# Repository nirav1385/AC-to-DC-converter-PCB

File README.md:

# ⚡ 12V AC to DC Converter — Full Bridge Rectifier PCB

A compact, through-hole **12V AC to DC converter** PCB designed in **KiCad 10.0**. This project converts 12V AC input into smooth DC output using a full-bridge rectifier with filtering, and includes a power indicator LED.

## 📸 Project Photos

### Schematic Diagram

### PCB Layout

### 3D View of PCB

---

## 📋 Table of Contents

- [Project Photos](#-project-photos)
- [Features](#-features)
- [Circuit Description](#-circuit-description)
- [Schematic Overview](#-schematic-overview)
- [Bill of Materials (BOM)](#-bill-of-materials-bom)
- [PCB Details](#-pcb-details)
- [How It Works](#-how-it-works)
- [Getting Started](#-getting-started)
- [Manufacturing](#-manufacturing)
- [Safety Warning](#%EF%B8%8F-safety-warning)
- [License](#-license)

---

## ✨ Features

- 🔌 **Full-bridge rectifier** using 4x 1N4007 diodes for efficient AC to DC conversion
- 🔋 **1000µF electrolytic capacitor** for smooth, ripple-free DC output
- 💡 **LED power indicator** with current-limiting resistor — know at a glance when the circuit is ON
- 🔩 **Screw terminal connectors** for easy and secure wire connections (both AC input & DC output)
- 📐 **Compact through-hole (THT) design** — easy to solder by hand, beginner-friendly
- 📦 **Gerber files included** — ready for PCB fabrication
- 🛠️ **Designed in KiCad 10.0** — fully open-source EDA tool

---

## 🔍 Circuit Description

This is a classic **unregulated AC to DC power supply** circuit. It takes a 12V AC input (typically from a step-down transformer) and converts it to approximately **~15-17V DC** (peak voltage minus diode drops) using a full-bridge rectifier.

---

## 📐 Schematic Overview

The circuit consists of the following stages:

### 1. AC Input Stage
- **J1** — Screw Terminal (2-pin) for 12V AC input from a transformer

### 2. Full-Bridge Rectifier
- **D1, D2, D3, D4** — 1N4007 (1000V, 1A) rectifier diodes arranged in a bridge configuration
- Converts both halves of the AC waveform into pulsating DC

### 3. Filtering Stage
- **C1** — 1000µF electrolytic capacitor
- Smooths the pulsating DC into a nearly constant DC voltage
- Reduces output ripple significantly

### 4. Bleeder/Discharge Resistor
- **R1** — 10kΩ resistor connected across the output
- Safely discharges the capacitor when the circuit is turned off
- Provides a minimum load for stability

### 5. Power Indicator
- **R2** — 2.2kΩ current-limiting resistor
- **D5** — LED (5mm, through-hole)
- Indicates that DC power is present at the output

### 6. DC Output Stage
- **J2** — Screw Terminal (2-pin) for DC output (+VE and -VE)

---

## 📦 Bill of Materials (BOM)

| Ref | Component | Value | Package/Footprint | Qty | Description |
|-----|-----------|-------|--------------------|-----|-------------|
| D1, D2, D3, D4 | 1N4007 | - | DO-41 (THT) | 4 | 1000V 1A General Purpose Rectifier Diode |
| D5 | LED | - | 5mm THT | 1 | Power Indicator LED |
| C1 | Electrolytic Capacitor | 1000µF | Radial D8.0mm P3.50mm | 1 | Filtering/Smoothing Capacitor |
| R1 | Resistor | 10kΩ | Axial DIN0204 (THT) | 1 | Bleeder/Discharge Resistor |
| R2 | Resistor | 2.2kΩ | Axial DIN0204 (THT) | 1 | LED Current-Limiting Resistor |
| J1 | Screw Terminal | 2-pin | MaiXu MX126 5.0mm pitch | 1 | AC Input Connector |
| J2 | Screw Terminal | 2-pin | MaiXu MX126 5.0mm pitch | 1 | DC Output Connector |

**Total Components: 9**

---

## 🖥️ PCB Details

| Parameter | Details |
|-----------|---------|
| **EDA Tool** | KiCad 10.0 |
| **Layers** | 1-layer (Front Copper) |
| **Components** | All Through-Hole (THT) |
| **Connectors** | Screw Terminals (5.0mm pitch) |
| **Solder Mask** | Both sides |
| **Silkscreen** | Both sides |

---

## ⚙️ How It Works

```
AC Input (12V AC)
      │
      ▼
┌──────────────┐
│   During positive half cycle:
│   Current flows: J1 Pin1 → D1 → +VE rail → Load → -VE rail → D4 → J1 Pin2
│
│   During negative half cycle:
│   Current flows: J1 Pin2 → D3 → +VE rail → Load → -VE rail → D2 → J1 Pin1
│
│   Result: Full-wave rectified pulsating DC
└──────────────┘
      │
      ▼
┌──────────────┐
│   C1 (1000µF) charges during voltage peaks and
│   discharges during valleys, smoothing the output
└──────────────┘
      │
      ▼
┌──────────────┐
│   R1 (10kΩ) provides a safe discharge path
│   R2 (2.2kΩ) + LED indicates power status
└──────────────┘
      │
      ▼
  DC Output (~15-17V DC)
```

### Output Voltage Calculation

```
V_out (peak) = V_ac(peak) - 2 × V_diode
             = (12 × √2) - (2 × 0.7)
             = 16.97 - 1.4
             ≈ 15.6V DC (peak)
```

### LED Current Calculation

```
I_LED = (V_out - V_LED) / R2
      = (15.6 - 2.0) / 2200
      ≈ 6.2 mA (safe operating current for LED)
```

---

## 🚀 Getting Started

### Prerequisites

- [KiCad 10.0](https://www.kicad.org/) or later (to open and edit the schematic/PCB files)

### Project Files

```
ac_to_dc_converter/
├── 📄 ac_to_dc_converter.kicad_pro    # KiCad project file
├── 📄 ac_to_dc_converter.kicad_sch    # Schematic file
├── 📄 ac_to_dc_converter.kicad_pcb    # PCB layout file
├── 📁 Gerber/                          # Manufacturing files (ready to fab)
│   ├── ac_to_dc_converter-F_Cu.gbr        # Front copper layer
│   ├── ac_to_dc_converter-B_Cu.gbr        # Back copper layer
│   ├── ac_to_dc_converter-F_Mask.gbr      # Front solder mask
│   ├── ac_to_dc_converter-B_Mask.gbr      # Back solder mask
│   ├── ac_to_dc_converter-F_Paste.gbr     # Front paste layer
│   ├── ac_to_dc_converter-B_Paste.gbr     # Back paste layer
│   ├── ac_to_dc_converter-F_Silkscreen.gbr# Front silkscreen
│   ├── ac_to_dc_converter-B_Silkscreen.gbr# Back silkscreen
│   ├── ac_to_dc_converter-Edge_Cuts.gbr   # Board outline
│   ├── ac_to_dc_converter-PTH.drl         # Plated through-holes drill
│   ├── ac_to_dc_converter-NPTH.drl        # Non-plated through-holes drill
│   └── ac_to_dc_converter-job.gbrjob      # Gerber job file
└── 📄 README.md                        # This file
```

### Opening the Project

1. Download or clone this repository
2. Open KiCad 10.0
3. Go to **File → Open Project**
4. Navigate to the project folder and select `ac_to_dc_converter.kicad_pro`

---

## 🏭 Manufacturing

The **Gerber files** are pre-generated and located in the `Gerber/` folder. You can directly upload the Gerber folder (as a ZIP) to any PCB manufacturer:

- [JLCPCB](https://jlcpcb.com/)
- [PCBWay](https://www.pcbway.com/)
- [OSH Park](https://oshpark.com/)
- [Seeed Studio Fusion](https://www.seeedstudio.com/fusion.html)

### Steps to Order:
1. Compress the `Gerber/` folder into a `.zip` file
2. Upload to your preferred PCB manufacturer's website
3. Select your desired options (color, quantity, thickness, etc.)
4. Place the order and wait for delivery! 🎉

---

## ⚠️ Safety Warning

> **⚡ CAUTION: This circuit deals with AC mains power (through a transformer). Always exercise proper safety precautions.**

- ❌ **DO NOT** connect this circuit directly to mains AC (220V/110V) — always use a proper step-down transformer
- ✅ Use a **12V AC transformer** as the input source
- 🔌 Always disconnect power before making any changes to the circuit
- 🛡️ This is an **unregulated** power supply — output voltage may vary with load
- 💡 For regulated output, consider adding a voltage regulator (e.g., LM7812 for 12V DC or LM7805 for 5V DC)
- 🔥 Ensure proper ventilation and do not exceed component ratings

---

## 🔧 Possible Improvements

- [ ] Add a **voltage regulator** (LM7812/LM7805) for stable regulated output
- [ ] Add **input fuse** for overcurrent protection
- [ ] Add **TVS diode** or **MOV** for surge protection
- [ ] Replace with **polarized capacitor symbol** for clarity
- [ ] Add **heat sink** provisions for high-current applications
- [ ] Design an **SMD version** for compact form factor

---

## 👨‍💻 Author

**Nirav Jain** — Designed with ❤️ using KiCad

---

## 📄 License

This project is open-source. Feel free to use, modify, and distribute.

---

<p align="center">
  <b>⭐ If you found this project helpful, please give it a star! ⭐</b>
</p>

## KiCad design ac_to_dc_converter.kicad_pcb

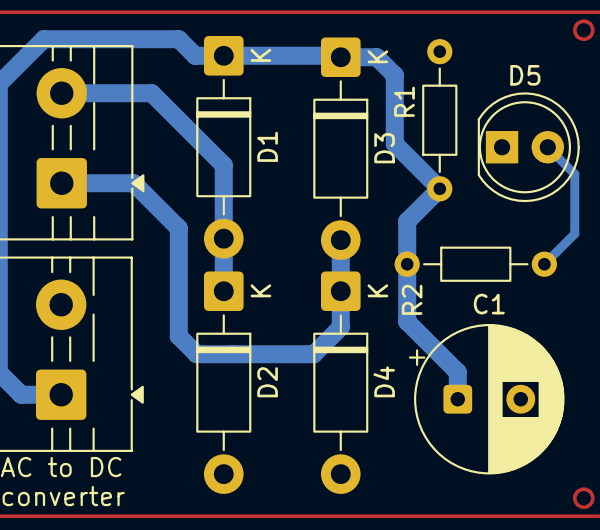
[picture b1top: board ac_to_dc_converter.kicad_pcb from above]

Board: 2 copper layers, 10 parts (0 on the bottom side), 5 nets.

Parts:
AC IN (J1): AC Supply; TerminalBlock_MaiXu_MX126-5.0-02P_1x02_P5.00mm
C1: 1000uf; CP_Radial_D8.0mm_P3.50mm
D1, D2, D3, D4: 1N4007; D_DO-41_SOD81_P10.16mm_Horizontal
D5: LED; LED_D5.0mm
DC OUT (J2): DC Supply; TerminalBlock_MaiXu_MX126-5.0-02P_1x02_P5.00mm
R1: 10k; R_Axial_DIN0204_L3.6mm_D1.6mm_P7.62mm_Horizontal
R2: 2.2k; R_Axial_DIN0204_L3.6mm_D1.6mm_P7.62mm_Horizontal

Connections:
/+VE: C1.1, D1.1 (K), D3.1 (K), DC OUT (J2).1, R1.1, R2.1
GND: C1.2, D2.2 (A), D4.2 (A), D5.1 (K), DC OUT (J2).2, R1.2
unnamed: AC IN (J1).2, D1.2 (A), D2.1 (K)
unnamed: AC IN (J1).1, D3.2 (A), D4.1 (K)
unnamed: D5.2 (A), R2.2
